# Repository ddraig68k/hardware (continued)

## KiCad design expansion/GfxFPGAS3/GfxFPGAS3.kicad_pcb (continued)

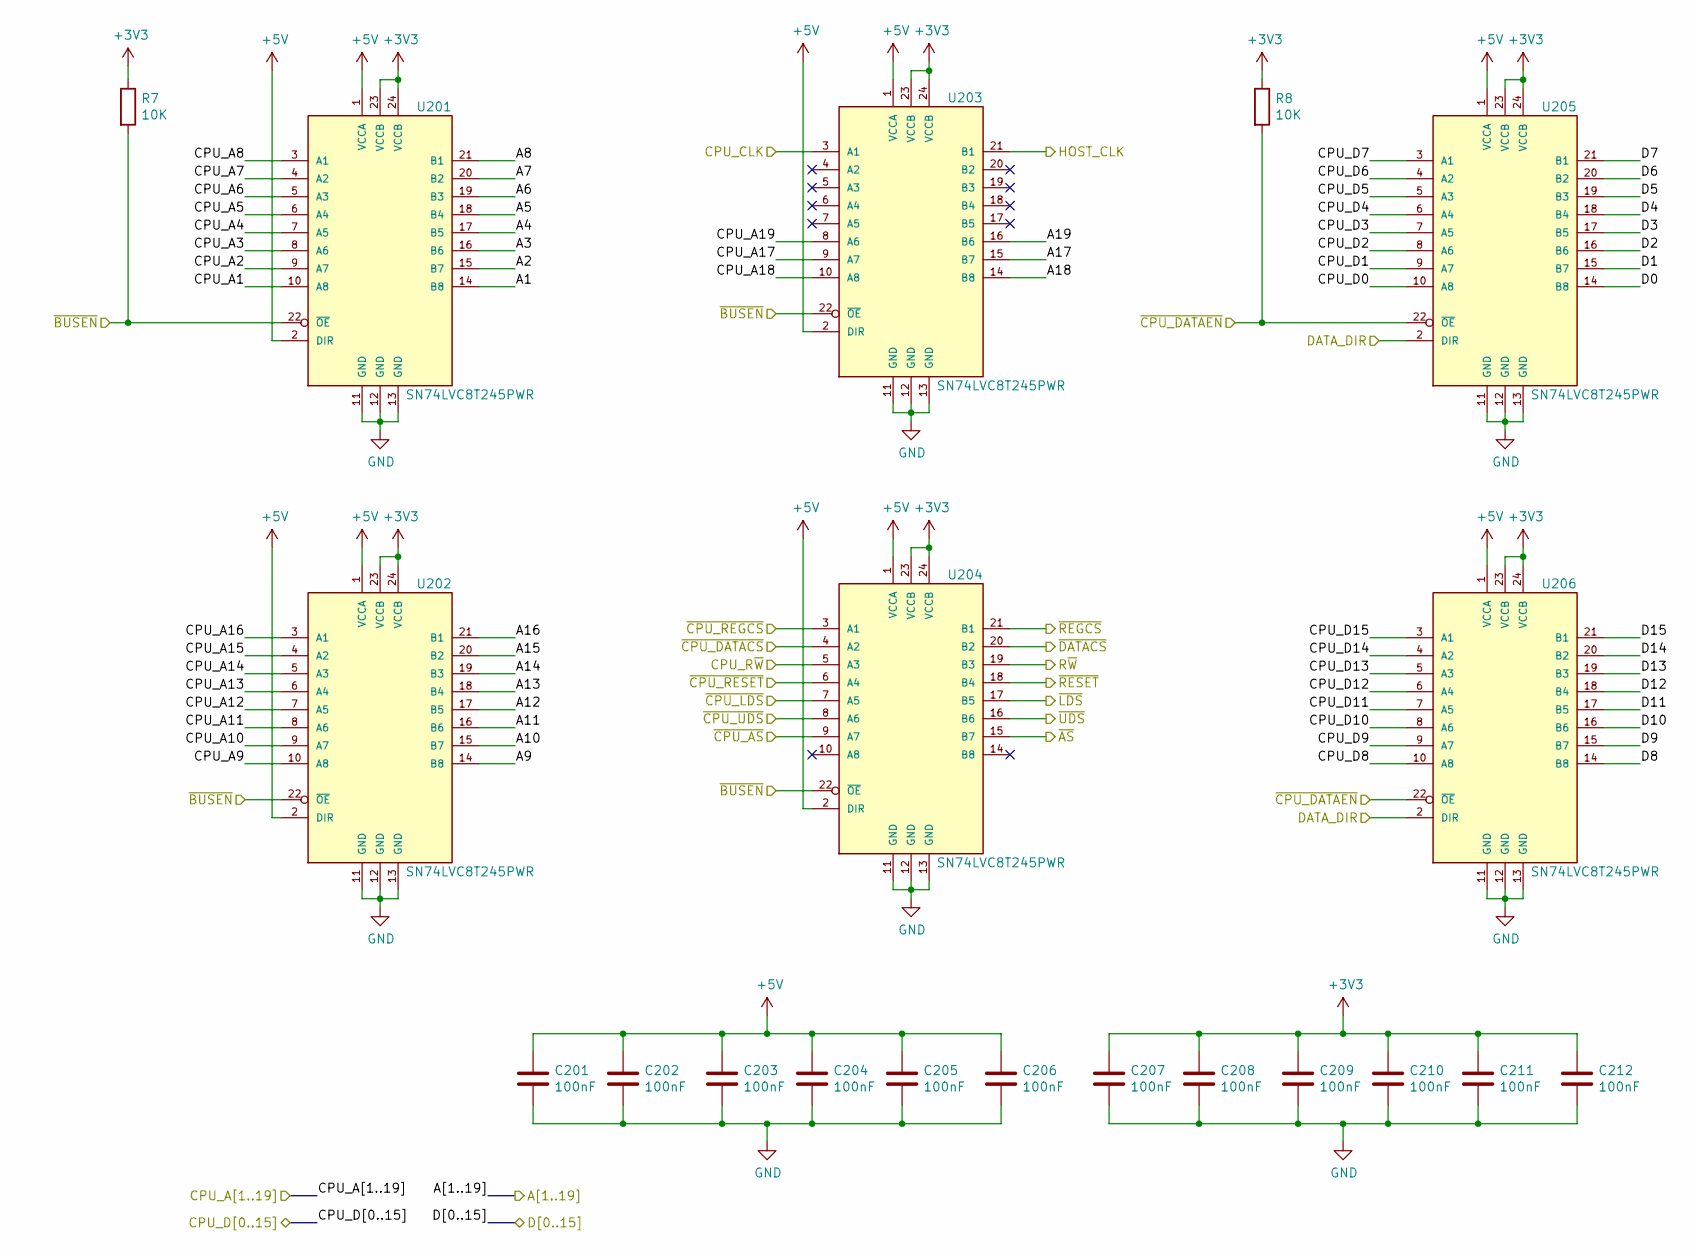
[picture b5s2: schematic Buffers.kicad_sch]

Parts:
C201, C202, C203, C204, C205, C206, C207, C208, C209, C210, C211, C212: 100nF; C_0805_2012Metric
R7, R8: 10K; R_0805_2012Metric
U201, U202, U203, U204, U205, U206: SN74LVC8T245PWR; SOP65P640X120-24N

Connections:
+5V: C201.1, C202.1, C203.1, C204.1, C205.1, C206.1, U201.1 (VCCA), U201.2 (DIR), U202.1 (VCCA), U202.2 (DIR), U203.1 (VCCA), U203.2 (DIR), U204.1 (VCCA), U204.2 (DIR), U205.1 (VCCA), U206.1 (VCCA); also elsewhere on the board
/CPU_A1: U201.10 (A8); also elsewhere on the board
/CPU_A2: U201.9 (A7); also elsewhere on the board
/CPU_A3: U201.8 (A6); also elsewhere on the board
/CPU_A4: U201.7 (A5); also elsewhere on the board
/CPU_A5: U201.6 (A4); also elsewhere on the board
/CPU_A6: U201.5 (A3); also elsewhere on the board
/CPU_A7: U201.4 (A2); also elsewhere on the board
/CPU_A8: U201.3 (A1); also elsewhere on the board
/CPU_A9: U202.10 (A8); also elsewhere on the board
/CPU_A10: U202.9 (A7); also elsewhere on the board
/CPU_A11: U202.8 (A6); also elsewhere on the board
/CPU_A12: U202.7 (A5); also elsewhere on the board
/CPU_A13: U202.6 (A4); also elsewhere on the board
/CPU_A14: U202.5 (A3); also elsewhere on the board
/CPU_A15: U202.4 (A2); also elsewhere on the board
/CPU_A16: U202.3 (A1); also elsewhere on the board
/CPU_A17: U203.9 (A7); also elsewhere on the board
/CPU_A18: U203.10 (A8); also elsewhere on the board
/CPU_A19: U203.8 (A6); also elsewhere on the board
/CPU_CLK: U203.3 (A1); also elsewhere on the board
/CPU_D0: U205.10 (A8); also elsewhere on the board
/CPU_D1: U205.9 (A7); also elsewhere on the board
/CPU_D2: U205.8 (A6); also elsewhere on the board
/CPU_D3: U205.7 (A5); also elsewhere on the board
/CPU_D4: U205.6 (A4); also elsewhere on the board
/CPU_D5: U205.5 (A3); also elsewhere on the board
/CPU_D6: U205.4 (A2); also elsewhere on the board
/CPU_D7: U205.3 (A1); also elsewhere on the board
/CPU_D8: U206.10 (A8); also elsewhere on the board
/CPU_D9: U206.9 (A7); also elsewhere on the board
/CPU_D10: U206.8 (A6); also elsewhere on the board
/CPU_D11: U206.7 (A5); also elsewhere on the board
/CPU_D12: U206.6 (A4); also elsewhere on the board
/CPU_D13: U206.5 (A3); also elsewhere on the board
/CPU_D14: U206.4 (A2); also elsewhere on the board
/CPU_D15: U206.3 (A1); also elsewhere on the board
/CPU_R~W: U204.5 (A3); also elsewhere on the board
/FPGA/A1: U201.14 (B8); also elsewhere on the board
/FPGA/A2: U201.15 (B7); also elsewhere on the board
/FPGA/A3: U201.16 (B6); also elsewhere on the board
/FPGA/A4: U201.17 (B5); also elsewhere on the board
/FPGA/A5: U201.18 (B4); also elsewhere on the board
/FPGA/A6: U201.19 (B3); also elsewhere on the board
/FPGA/A7: U201.20 (B2); also elsewhere on the board
/FPGA/A8: U201.21 (B1); also elsewhere on the board
/FPGA/A9: U202.14 (B8); also elsewhere on the board
/FPGA/A10: U202.15 (B7); also elsewhere on the board
/FPGA/A11: U202.16 (B6); also elsewhere on the board
/FPGA/A12: U202.17 (B5); also elsewhere on the board
/FPGA/A13: U202.18 (B4); also elsewhere on the board
/FPGA/A14: U202.19 (B3); also elsewhere on the board
/FPGA/A15: U202.20 (B2); also elsewhere on the board
/FPGA/A16: U202.21 (B1); also elsewhere on the board
/FPGA/A17: U203.15 (B7); also elsewhere on the board
/FPGA/A18: U203.14 (B8); also elsewhere on the board
/FPGA/A19: U203.16 (B6); also elsewhere on the board
/FPGA/D0: U205.14 (B8); also elsewhere on the board
/FPGA/D1: U205.15 (B7); also elsewhere on the board
/FPGA/D2: U205.16 (B6); also elsewhere on the board
/FPGA/D3: U205.17 (B5); also elsewhere on the board
/FPGA/D4: U205.18 (B4); also elsewhere on the board
/FPGA/D5: U205.19 (B3); also elsewhere on the board
/FPGA/D6: U205.20 (B2); also elsewhere on the board
/FPGA/D7: U205.21 (B1); also elsewhere on the board
/FPGA/D8: U206.14 (B8); also elsewhere on the board
/FPGA/D9: U206.15 (B7); also elsewhere on the board
/FPGA/D10: U206.16 (B6); also elsewhere on the board
/FPGA/D11: U206.17 (B5); also elsewhere on the board
/FPGA/D12: U206.18 (B4); also elsewhere on the board
/FPGA/D13: U206.19 (B3); also elsewhere on the board
/FPGA/D14: U206.20 (B2); also elsewhere on the board
/FPGA/D15: U206.21 (B1); also elsewhere on the board
/FPGA/DATA_DIR: U205.2 (DIR), U206.2 (DIR); also elsewhere on the board
/FPGA/HOST_CLK: U203.21 (B1); also elsewhere on the board
/FPGA/R~W: U204.19 (B3); also elsewhere on the board
/FPGA/~AS: U204.15 (B7); also elsewhere on the board
/FPGA/~BUSEN: R7.2, U201.22 (~OE), U202.22 (~OE), U203.22 (~OE), U204.22 (~OE); also elsewhere on the board
/FPGA/~CPU_DATAEN: R8.2, U205.22 (~OE), U206.22 (~OE); also elsewhere on the board
/FPGA/~DATACS: U204.20 (B2); also elsewhere on the board
/FPGA/~LDS: U204.17 (B5); also elsewhere on the board
/FPGA/~REGCS: U204.21 (B1); also elsewhere on the board
/FPGA/~RESET: U204.18 (B4); also elsewhere on the board
/FPGA/~UDS: U204.16 (B6); also elsewhere on the board
/~CPU_AS: U204.9 (A7); also elsewhere on the board
/~CPU_DATACS: U204.4 (A2); also elsewhere on the board
/~CPU_LDS: U204.7 (A5); also elsewhere on the board
/~CPU_REGCS: U204.3 (A1); also elsewhere on the board
/~CPU_RESET: U204.6 (A4); also elsewhere on the board
/~CPU_UDS: U204.8 (A6); also elsewhere on the board
GND: C201.2, C202.2, C203.2, C204.2, C205.2, C206.2, C207.2, C208.2, C209.2, C210.2, C211.2, C212.2, U201.11 (GND), U201.12 (GND), U201.13 (GND), U202.11 (GND), U202.12 (GND), U202.13 (GND), U203.11 (GND), U203.12 (GND), U203.13 (GND), U204.11 (GND), U204.12 (GND), U204.13 (GND), U205.11 (GND), U205.12 (GND), U205.13 (GND), U206.11 (GND), U206.12 (GND), U206.13 (GND); also elsewhere on the board

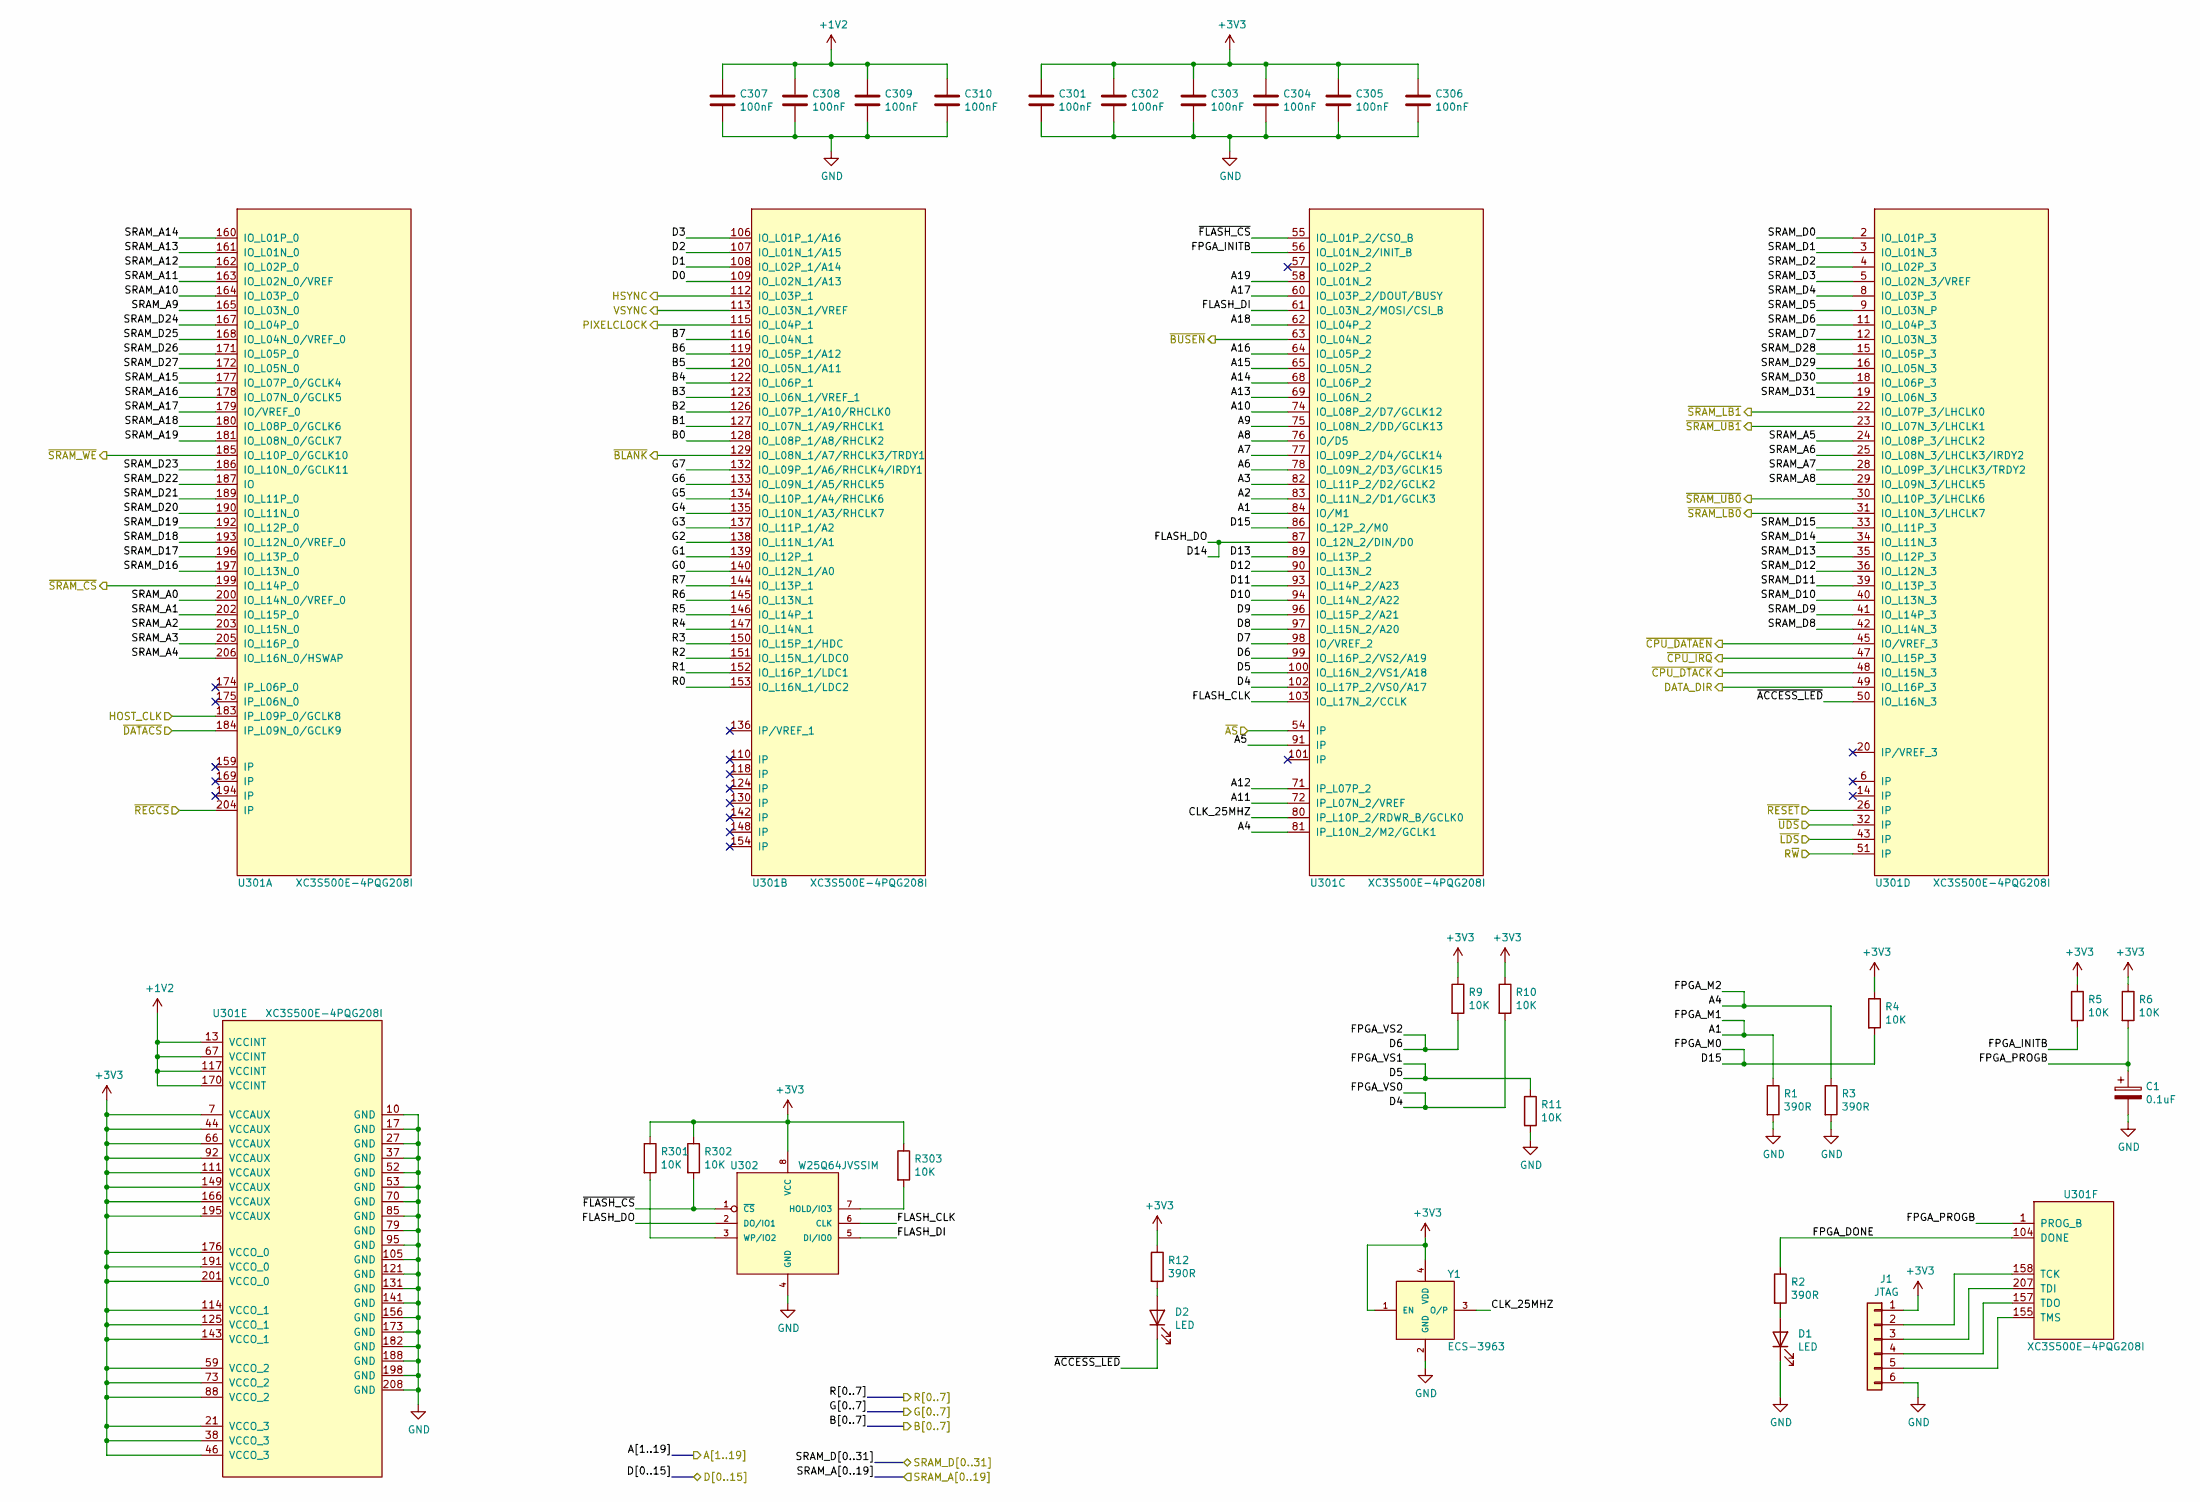
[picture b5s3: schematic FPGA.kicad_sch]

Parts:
C1: 0.1uF; CP_Elec_4x5.3
C301, C302, C303, C304, C305, C306, C307, C308, C309, C310: 100nF; C_0805_2012Metric
D1, D2: LED; LED_1206_3216Metric
J1: JTAG; PinHeader_1x06_P2.54mm_Vertical
R1, R2, R3, R12: 390R; R_0805_2012Metric
R4, R5, R6, R9, R10, R11, R301, R302, R303: 10K; R_0805_2012Metric
U301: XC3S500E-4PQG208I; QFP50P3060X3060X409-208N
U302: W25Q64JVSSIM; SOIC127P790X195-8N
Y1: ECS-3963; OSC_ECS-3963; PARTREV N/A

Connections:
+1V2: C307.1, C308.1, C309.1, C310.1, U301.13 (VCCINT), U301.67 (VCCINT), U301.117 (VCCINT), U301.170 (VCCINT); also elsewhere on the board
/FPGA/A1: R1.1, U301.84 (IO/M1); also elsewhere on the board
/FPGA/A2: U301.83 (IO_L11N_2/D1/GCLK3); also elsewhere on the board
/FPGA/A3: U301.82 (IO_L11P_2/D2/GCLK2); also elsewhere on the board
/FPGA/A4: R3.1, U301.81 (IP_L10N_2/M2/GCLK1); also elsewhere on the board
/FPGA/A5: U301.91 (IP); also elsewhere on the board
/FPGA/A6: U301.78 (IO_L09N_2/D3/GCLK15); also elsewhere on the board
/FPGA/A7: U301.77 (IO_L09P_2/D4/GCLK14); also elsewhere on the board
/FPGA/A8: U301.76 (IO/D5); also elsewhere on the board
/FPGA/A9: U301.75 (IO_L08N_2/DD/GCLK13); also elsewhere on the board
/FPGA/A10: U301.74 (IO_L08P_2/D7/GCLK12); also elsewhere on the board
/FPGA/A11: U301.72 (IP_L07N_2/VREF); also elsewhere on the board
/FPGA/A12: U301.71 (IP_L07P_2); also elsewhere on the board
/FPGA/A13: U301.69 (IO_L06N_2); also elsewhere on the board
/FPGA/A14: U301.68 (IO_L06P_2); also elsewhere on the board
/FPGA/A15: U301.65 (IO_L05N_2); also elsewhere on the board
/FPGA/A16: U301.64 (IO_L05P_2); also elsewhere on the board
/FPGA/A17: U301.60 (IO_L03P_2/DOUT/BUSY); also elsewhere on the board
/FPGA/A18: U301.62 (IO_L04P_2); also elsewhere on the board
/FPGA/A19: U301.58 (IO_L01N_2); also elsewhere on the board
/FPGA/B0: U301.128 (IO_L08P_1/A8/RHCLK2); also elsewhere on the board
/FPGA/B1: U301.127 (IO_L07N_1/A9/RHCLK1); also elsewhere on the board
/FPGA/B2: U301.126 (IO_L07P_1/A10/RHCLK0); also elsewhere on the board
/FPGA/B3: U301.123 (IO_L06N_1/VREF_1); also elsewhere on the board
/FPGA/B4: U301.122 (IO_L06P_1); also elsewhere on the board
/FPGA/B5: U301.120 (IO_L05N_1/A11); also elsewhere on the board
/FPGA/B6: U301.119 (IO_L05P_1/A12); also elsewhere on the board
/FPGA/B7: U301.116 (IO_L04N_1); also elsewhere on the board
/FPGA/CLK_25MHZ: U301.80 (IP_L10P_2/RDWR_B/GCLK0), Y1.3 (O/P)
/FPGA/D0: U301.109 (IO_L02N_1/A13); also elsewhere on the board
/FPGA/D1: U301.108 (IO_L02P_1/A14); also elsewhere on the board
/FPGA/D2: U301.107 (IO_L01N_1/A15); also elsewhere on the board
/FPGA/D3: U301.106 (IO_L01P_1/A16); also elsewhere on the board
/FPGA/D4: R10.2, U301.102 (IO_L17P_2/VS0/A17); also elsewhere on the board
/FPGA/D5: R11.1, U301.100 (IO_L16N_2/VS1/A18); also elsewhere on the board
/FPGA/D6: R9.2, U301.99 (IO_L16P_2/VS2/A19); also elsewhere on the board
/FPGA/D7: U301.98 (IO/VREF_2); also elsewhere on the board
/FPGA/D8: U301.97 (IO_L15N_2/A20); also elsewhere on the board
/FPGA/D9: U301.96 (IO_L15P_2/A21); also elsewhere on the board
/FPGA/D10: U301.94 (IO_L14N_2/A22); also elsewhere on the board
/FPGA/D11: U301.93 (IO_L14P_2/A23); also elsewhere on the board
/FPGA/D12: U301.90 (IO_L13N_2); also elsewhere on the board
/FPGA/D13: U301.89 (IO_L13P_2); also elsewhere on the board
/FPGA/D14: U301.87 (IO_12N_2/DIN/D0), U302.2 (DO/IO1); also elsewhere on the board
/FPGA/D15: R4.2, U301.86 (IO_12P_2/M0); also elsewhere on the board
/FPGA/DATA_DIR: U301.49 (IO_L16P_3); also elsewhere on the board
/FPGA/FLASH_CLK: U301.103 (IO_L17N_2/CCLK), U302.6 (CLK)
/FPGA/FLASH_DI: U301.61 (IO_L03N_2/MOSI/CSI_B), U302.5 (DI/IO0)
/FPGA/FPGA_DONE: R2.1, U301.104 (DONE)
/FPGA/FPGA_INITB: R5.2, U301.56 (IO_L01N_2/INIT_B)
/FPGA/FPGA_PROGB: C1.1, R6.2, U301.1 (PROG_B)
/FPGA/G0: U301.140 (IO_L12N_1/A0); also elsewhere on the board
/FPGA/G1: U301.139 (IO_L12P_1); also elsewhere on the board
/FPGA/G2: U301.138 (IO_L11N_1/A1); also elsewhere on the board
/FPGA/G3: U301.137 (IO_L11P_1/A2); also elsewhere on the board
/FPGA/G4: U301.135 (IO_L10N_1/A3/RHCLK7); also elsewhere on the board
/FPGA/G5: U301.134 (IO_L10P_1/A4/RHCLK6); also elsewhere on the board
/FPGA/G6: U301.133 (IO_L09N_1/A5/RHCLK5); also elsewhere on the board
/FPGA/G7: U301.132 (IO_L09P_1/A6/RHCLK4/IRDY1); also elsewhere on the board
/FPGA/HOST_CLK: U301.183 (IP_L09P_0/GCLK8); also elsewhere on the board
/FPGA/HSYNC: U301.112 (IO_L03P_1); also elsewhere on the board
/FPGA/PIXELCLOCK: U301.115 (IO_L04P_1); also elsewhere on the board
/FPGA/R0: U301.153 (IO_L16N_1/LDC2); also elsewhere on the board
/FPGA/R1: U301.152 (IO_L16P_1/LDC1); also elsewhere on the board
/FPGA/R2: U301.151 (IO_L15N_1/LDC0); also elsewhere on the board
/FPGA/R3: U301.150 (IO_L15P_1/HDC); also elsewhere on the board
/FPGA/R4: U301.147 (IO_L14N_1); also elsewhere on the board
/FPGA/R5: U301.146 (IO_L14P_1); also elsewhere on the board
/FPGA/R6: U301.145 (IO_L13N_1); also elsewhere on the board
/FPGA/R7: U301.144 (IO_L13P_1); also elsewhere on the board
/FPGA/R~W: U301.51 (IP); also elsewhere on the board
/FPGA/SRAM_A0: U301.200 (IO_L14N_0/VREF_0); also elsewhere on the board
/FPGA/SRAM_A1: U301.202 (IO_L15P_0); also elsewhere on the board
/FPGA/SRAM_A2: U301.203 (IO_L15N_0); also elsewhere on the board
/FPGA/SRAM_A3: U301.205 (IO_L16P_0); also elsewhere on the board
/FPGA/SRAM_A4: U301.206 (IO_L16N_0/HSWAP); also elsewhere on the board
/FPGA/SRAM_A5: U301.24 (IO_L08P_3/LHCLK2); also elsewhere on the board
/FPGA/SRAM_A6: U301.25 (IO_L08N_3/LHCLK3/IRDY2); also elsewhere on the board
/FPGA/SRAM_A7: U301.28 (IO_L09P_3/LHCLK3/TRDY2); also elsewhere on the board
/FPGA/SRAM_A8: U301.29 (IO_L09N_3/LHCLK5); also elsewhere on the board
/FPGA/SRAM_A9: U301.165 (IO_L03N_0); also elsewhere on the board
/FPGA/SRAM_A10: U301.164 (IO_L03P_0); also elsewhere on the board
/FPGA/SRAM_A11: U301.163 (IO_L02N_0/VREF); also elsewhere on the board
/FPGA/SRAM_A12: U301.162 (IO_L02P_0); also elsewhere on the board
/FPGA/SRAM_A13: U301.161 (IO_L01N_0); also elsewhere on the board
/FPGA/SRAM_A14: U301.160 (IO_L01P_0); also elsewhere on the board
/FPGA/SRAM_A15: U301.177 (IO_L07P_0/GCLK4); also elsewhere on the board
/FPGA/SRAM_A16: U301.178 (IO_L07N_0/GCLK5); also elsewhere on the board
/FPGA/SRAM_A17: U301.179 (IO/VREF_0); also elsewhere on the board
/FPGA/SRAM_A18: U301.180 (IO_L08P_0/GCLK6); also elsewhere on the board
/FPGA/SRAM_A19: U301.181 (IO_L08N_0/GCLK7); also elsewhere on the board
/FPGA/SRAM_D0: U301.2 (IO_L01P_3); also elsewhere on the board
/FPGA/SRAM_D1: U301.3 (IO_L01N_3); also elsewhere on the board
/FPGA/SRAM_D2: U301.4 (IO_L02P_3); also elsewhere on the board
/FPGA/SRAM_D3: U301.5 (IO_L02N_3/VREF); also elsewhere on the board
/FPGA/SRAM_D4: U301.8 (IO_L03P_3); also elsewhere on the board
/FPGA/SRAM_D5: U301.9 (IO_L03N_P); also elsewhere on the board
/FPGA/SRAM_D6: U301.11 (IO_L04P_3); also elsewhere on the board
/FPGA/SRAM_D7: U301.12 (IO_L03N_3); also elsewhere on the board
/FPGA/SRAM_D8: U301.42 (IO_L14N_3); also elsewhere on the board
/FPGA/SRAM_D9: U301.41 (IO_L14P_3); also elsewhere on the board
/FPGA/SRAM_D10: U301.40 (IO_L13N_3); also elsewhere on the board
/FPGA/SRAM_D11: U301.39 (IO_L13P_3); also elsewhere on the board
/FPGA/SRAM_D12: U301.36 (IO_L12N_3); also elsewhere on the board
/FPGA/SRAM_D13: U301.35 (IO_L12P_3); also elsewhere on the board
/FPGA/SRAM_D14: U301.34 (IO_L11N_3); also elsewhere on the board
/FPGA/SRAM_D15: U301.33 (IO_L11P_3); also elsewhere on the board
/FPGA/SRAM_D16: U301.197 (IO_L13N_0); also elsewhere on the board
/FPGA/SRAM_D17: U301.196 (IO_L13P_0); also elsewhere on the board
/FPGA/SRAM_D18: U301.193 (IO_L12N_0/VREF_0); also elsewhere on the board
/FPGA/SRAM_D19: U301.192 (IO_L12P_0); also elsewhere on the board
/FPGA/SRAM_D20: U301.190 (IO_L11N_0); also elsewhere on the board
/FPGA/SRAM_D21: U301.189 (IO_L11P_0); also elsewhere on the board
/FPGA/SRAM_D22: U301.187 (IO); also elsewhere on the board
/FPGA/SRAM_D23: U301.186 (IO_L10N_0/GCLK11); also elsewhere on the board
/FPGA/SRAM_D24: U301.167 (IO_L04P_0); also elsewhere on the board
/FPGA/SRAM_D25: U301.168 (IO_L04N_0/VREF_0); also elsewhere on the board
/FPGA/SRAM_D26: U301.171 (IO_L05P_0); also elsewhere on the board
/FPGA/SRAM_D27: U301.172 (IO_L05N_0); also elsewhere on the board
/FPGA/SRAM_D28: U301.15 (IO_L05P_3); also elsewhere on the board
/FPGA/SRAM_D29: U301.16 (IO_L05N_3); also elsewhere on the board
/FPGA/SRAM_D30: U301.18 (IO_L06P_3); also elsewhere on the board
/FPGA/SRAM_D31: U301.19 (IO_L06N_3); also elsewhere on the board
/FPGA/VSYNC: U301.113 (IO_L03N_1/VREF); also elsewhere on the board
/FPGA/~ACCESS_LED: D2.1 (K), U301.50 (IO_L16N_3)
/FPGA/~AS: U301.54 (IP); also elsewhere on the board
/FPGA/~BLANK: U301.129 (IO_L08N_1/A7/RHCLK3/TRDY1); also elsewhere on the board
/FPGA/~BUSEN: U301.63 (IO_L04N_2); also elsewhere on the board
/FPGA/~CPU_DATAEN: U301.45 (IO/VREF_3); also elsewhere on the board
/FPGA/~DATACS: U301.184 (IP_L09N_0/GCLK9); also elsewhere on the board
/FPGA/~FLASH_CS: R302.2, U301.55 (IO_L01P_2/CSO_B), U302.1 (~CS)
/FPGA/~LDS: U301.43 (IP); also elsewhere on the board
/FPGA/~REGCS: U301.204 (IP); also elsewhere on the board
/FPGA/~RESET: U301.26 (IP); also elsewhere on the board
/FPGA/~SRAM_CS: U301.199 (IO_L14P_0); also elsewhere on the board
/FPGA/~SRAM_LB0: U301.31 (IO_L10N_3/LHCLK7); also elsewhere on the board
/FPGA/~SRAM_LB1: U301.22 (IO_L07P_3/LHCLK0); also elsewhere on the board
/FPGA/~SRAM_UB0: U301.30 (IO_L10P_3/LHCLK6); also elsewhere on the board
/FPGA/~SRAM_UB1: U301.23 (IO_L07N_3/LHCLK1); also elsewhere on the board
/FPGA/~SRAM_WE: U301.185 (IO_L10P_0/GCLK10); also elsewhere on the board
/FPGA/~UDS: U301.32 (IP); also elsewhere on the board
/~CPU_DTACK: U301.48 (IO_L15N_3); also elsewhere on the board
/~CPU_IRQ: U301.47 (IO_L15P_3); also elsewhere on the board
GND: C1.2, C301.2, C302.2, C303.2, C304.2, C305.2, C306.2, C307.2, C308.2, C309.2, C310.2, D1.1 (K), J1.6, R1.2, R3.2, R11.2, U301.10 (GND), U301.17 (GND), U301.27 (GND), U301.37 (GND), U301.52 (GND), U301.53 (GND), U301.70 (GND), U301.79 (GND), U301.85 (GND), U301.95 (GND), U301.105 (GND), U301.121 (GND), U301.131 (GND), U301.141 (GND), U301.156 (GND), U301.173 (GND), U301.182 (GND), U301.188 (GND), U301.198 (GND), U301.208 (GND), U302.4 (GND), Y1.2 (GND); also elsewhere on the board
unnamed: D1.2 (A), R2.2
unnamed: D2.2 (A), R12.2
unnamed: J1.2, U301.158 (TCK)
unnamed: J1.3, U301.207 (TDI)
unnamed: J1.4, U301.157 (TDO)
unnamed: J1.5, U301.155 (TMS)
unnamed: R301.2, U302.3 (WP/IO2)
unnamed: R303.2, U302.7 (HOLD/IO3)

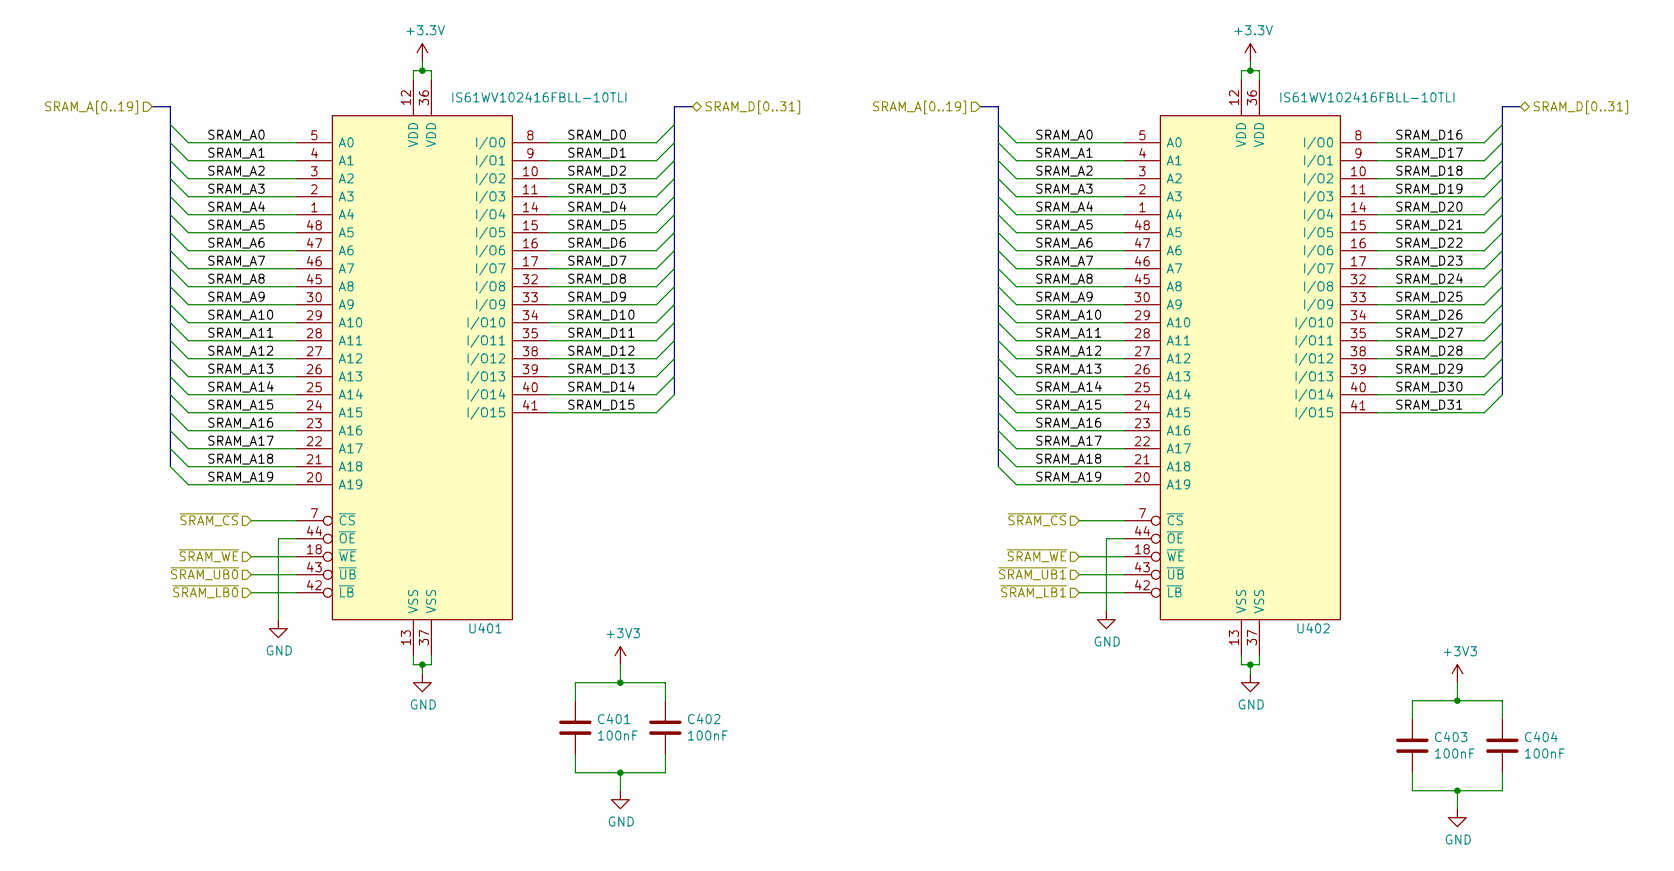
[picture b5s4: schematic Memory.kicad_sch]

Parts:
C401, C402, C403, C404: 100nF; C_0805_2012Metric
U401, U402: IS61WV102416FBLL-10TLI; SOP50P2000X120-48N; Manufacturer_Part_Number IS61WV102416FBLL-10TLI; Mouser Part Number 870-61WV12416FBL1TLI

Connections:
/FPGA/SRAM_A0: U401.5 (A0), U402.5 (A0); also elsewhere on the board
/FPGA/SRAM_A1: U401.4 (A1), U402.4 (A1); also elsewhere on the board
/FPGA/SRAM_A2: U401.3 (A2), U402.3 (A2); also elsewhere on the board
/FPGA/SRAM_A3: U401.2 (A3), U402.2 (A3); also elsewhere on the board
/FPGA/SRAM_A4: U401.1 (A4), U402.1 (A4); also elsewhere on the board
/FPGA/SRAM_A5: U401.48 (A5), U402.48 (A5); also elsewhere on the board
/FPGA/SRAM_A6: U401.47 (A6), U402.47 (A6); also elsewhere on the board
/FPGA/SRAM_A7: U401.46 (A7), U402.46 (A7); also elsewhere on the board
/FPGA/SRAM_A8: U401.45 (A8), U402.45 (A8); also elsewhere on the board
/FPGA/SRAM_A9: U401.30 (A9), U402.30 (A9); also elsewhere on the board
/FPGA/SRAM_A10: U401.29 (A10), U402.29 (A10); also elsewhere on the board
/FPGA/SRAM_A11: U401.28 (A11), U402.28 (A11); also elsewhere on the board
/FPGA/SRAM_A12: U401.27 (A12), U402.27 (A12); also elsewhere on the board
/FPGA/SRAM_A13: U401.26 (A13), U402.26 (A13); also elsewhere on the board
/FPGA/SRAM_A14: U401.25 (A14), U402.25 (A14); also elsewhere on the board
/FPGA/SRAM_A15: U401.24 (A15), U402.24 (A15); also elsewhere on the board
/FPGA/SRAM_A16: U401.23 (A16), U402.23 (A16); also elsewhere on the board
/FPGA/SRAM_A17: U401.22 (A17), U402.22 (A17); also elsewhere on the board
/FPGA/SRAM_A18: U401.21 (A18), U402.21 (A18); also elsewhere on the board
/FPGA/SRAM_A19: U401.20 (A19), U402.20 (A19); also elsewhere on the board
/FPGA/SRAM_D0: U401.8 (I/O0); also elsewhere on the board
/FPGA/SRAM_D1: U401.9 (I/O1); also elsewhere on the board
/FPGA/SRAM_D2: U401.10 (I/O2); also elsewhere on the board
/FPGA/SRAM_D3: U401.11 (I/O3); also elsewhere on the board
/FPGA/SRAM_D4: U401.14 (I/O4); also elsewhere on the board
/FPGA/SRAM_D5: U401.15 (I/O5); also elsewhere on the board
/FPGA/SRAM_D6: U401.16 (I/O6); also elsewhere on the board
/FPGA/SRAM_D7: U401.17 (I/O7); also elsewhere on the board
/FPGA/SRAM_D8: U401.32 (I/O8); also elsewhere on the board
/FPGA/SRAM_D9: U401.33 (I/O9); also elsewhere on the board
/FPGA/SRAM_D10: U401.34 (I/O10); also elsewhere on the board
/FPGA/SRAM_D11: U401.35 (I/O11); also elsewhere on the board
/FPGA/SRAM_D12: U401.38 (I/O12); also elsewhere on the board
/FPGA/SRAM_D13: U401.39 (I/O13); also elsewhere on the board
/FPGA/SRAM_D14: U401.40 (I/O14); also elsewhere on the board
/FPGA/SRAM_D15: U401.41 (I/O15); also elsewhere on the board
/FPGA/SRAM_D16: U402.8 (I/O0); also elsewhere on the board
/FPGA/SRAM_D17: U402.9 (I/O1); also elsewhere on the board
/FPGA/SRAM_D18: U402.10 (I/O2); also elsewhere on the board
/FPGA/SRAM_D19: U402.11 (I/O3); also elsewhere on the board
/FPGA/SRAM_D20: U402.14 (I/O4); also elsewhere on the board
/FPGA/SRAM_D21: U402.15 (I/O5); also elsewhere on the board
/FPGA/SRAM_D22: U402.16 (I/O6); also elsewhere on the board
/FPGA/SRAM_D23: U402.17 (I/O7); also elsewhere on the board
/FPGA/SRAM_D24: U402.32 (I/O8); also elsewhere on the board
/FPGA/SRAM_D25: U402.33 (I/O9); also elsewhere on the board
/FPGA/SRAM_D26: U402.34 (I/O10); also elsewhere on the board
/FPGA/SRAM_D27: U402.35 (I/O11); also elsewhere on the board
/FPGA/SRAM_D28: U402.38 (I/O12); also elsewhere on the board
/FPGA/SRAM_D29: U402.39 (I/O13); also elsewhere on the board
/FPGA/SRAM_D30: U402.40 (I/O14); also elsewhere on the board
/FPGA/SRAM_D31: U402.41 (I/O15); also elsewhere on the board
/FPGA/~SRAM_CS: U401.7 (~CS), U402.7 (~CS); also elsewhere on the board
/FPGA/~SRAM_LB0: U401.42 (~LB); also elsewhere on the board
/FPGA/~SRAM_LB1: U402.42 (~LB); also elsewhere on the board
/FPGA/~SRAM_UB0: U401.43 (~UB); also elsewhere on the board
/FPGA/~SRAM_UB1: U402.43 (~UB); also elsewhere on the board
/FPGA/~SRAM_WE: U401.18 (~WE), U402.18 (~WE); also elsewhere on the board
GND: C401.2, C402.2, C403.2, C404.2, U401.13 (VSS), U401.37 (VSS), U401.44 (~OE), U402.13 (VSS), U402.37 (VSS), U402.44 (~OE); also elsewhere on the board

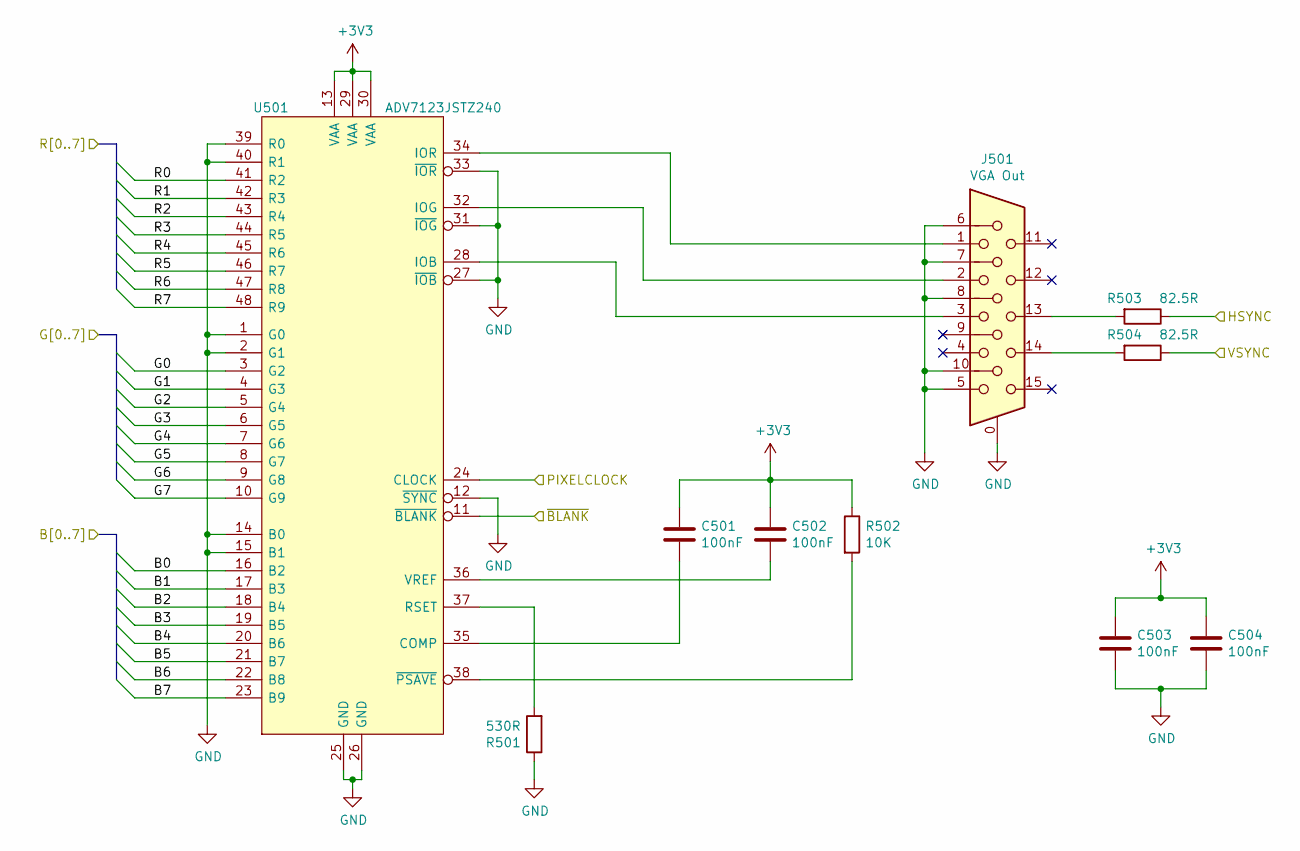
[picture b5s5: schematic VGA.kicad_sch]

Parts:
C501, C502, C503, C504: 100nF; C_0805_2012Metric
J501: VGA Out; DSUB-15-HD_Female_Horizontal_P2.29x1.98mm_EdgePinOffset3.03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
R501: 530R; R_0805_2012Metric
R502: 10K; R_0805_2012Metric
R503, R504: 82.5R; R_0805_2012Metric
U501: ADV7123JSTZ240; QFP50P900X900X160-48N; Manufacturer_Part_Number ADV7123JSTZ240; Mouser Part Number 584-ADV7123JSTZ240

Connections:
/FPGA/B0: U501.16 (B2); also elsewhere on the board
/FPGA/B1: U501.17 (B3); also elsewhere on the board
/FPGA/B2: U501.18 (B4); also elsewhere on the board
/FPGA/B3: U501.19 (B5); also elsewhere on the board
/FPGA/B4: U501.20 (B6); also elsewhere on the board
/FPGA/B5: U501.21 (B7); also elsewhere on the board
/FPGA/B6: U501.22 (B8); also elsewhere on the board
/FPGA/B7: U501.23 (B9); also elsewhere on the board
/FPGA/G0: U501.3 (G2); also elsewhere on the board
/FPGA/G1: U501.4 (G3); also elsewhere on the board
/FPGA/G2: U501.5 (G4); also elsewhere on the board
/FPGA/G3: U501.6 (G5); also elsewhere on the board
/FPGA/G4: U501.7 (G6); also elsewhere on the board
/FPGA/G5: U501.8 (G7); also elsewhere on the board
/FPGA/G6: U501.9 (G8); also elsewhere on the board
/FPGA/G7: U501.10 (G9); also elsewhere on the board
/FPGA/HSYNC: R503.1; also elsewhere on the board
/FPGA/PIXELCLOCK: U501.24 (CLOCK); also elsewhere on the board
/FPGA/R0: U501.41 (R2); also elsewhere on the board
/FPGA/R1: U501.42 (R3); also elsewhere on the board
/FPGA/R2: U501.43 (R4); also elsewhere on the board
/FPGA/R3: U501.44 (R5); also elsewhere on the board
/FPGA/R4: U501.45 (R6); also elsewhere on the board
/FPGA/R5: U501.46 (R7); also elsewhere on the board
/FPGA/R6: U501.47 (R8); also elsewhere on the board
/FPGA/R7: U501.48 (R9); also elsewhere on the board
/FPGA/VSYNC: R504.1; also elsewhere on the board
/FPGA/~BLANK: U501.11 (~BLANK); also elsewhere on the board
GND: C503.2, C504.2, J501.0, J501.5, J501.6, J501.7, J501.8, J501.10, R501.1, U501.1 (G0), U501.2 (G1), U501.12 (~SYNC), U501.14 (B0), U501.15 (B1), U501.25 (GND), U501.26 (GND), U501.27 (~IOB), U501.31 (~IOG), U501.33 (~IOR), U501.39 (R0), U501.40 (R1); also elsewhere on the board
unnamed: C501.2, U501.35 (COMP)
unnamed: C502.2, U501.36 (VREF)
unnamed: J501.1, U501.34 (IOR)
unnamed: J501.2, U501.32 (IOG)
unnamed: J501.3, U501.28 (IOB)
unnamed: J501.13, R503.2
unnamed: J501.14, R504.2
unnamed: R501.2, U501.37 (RSET)
unnamed: R502.2, U501.38 (~PSAVE)

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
